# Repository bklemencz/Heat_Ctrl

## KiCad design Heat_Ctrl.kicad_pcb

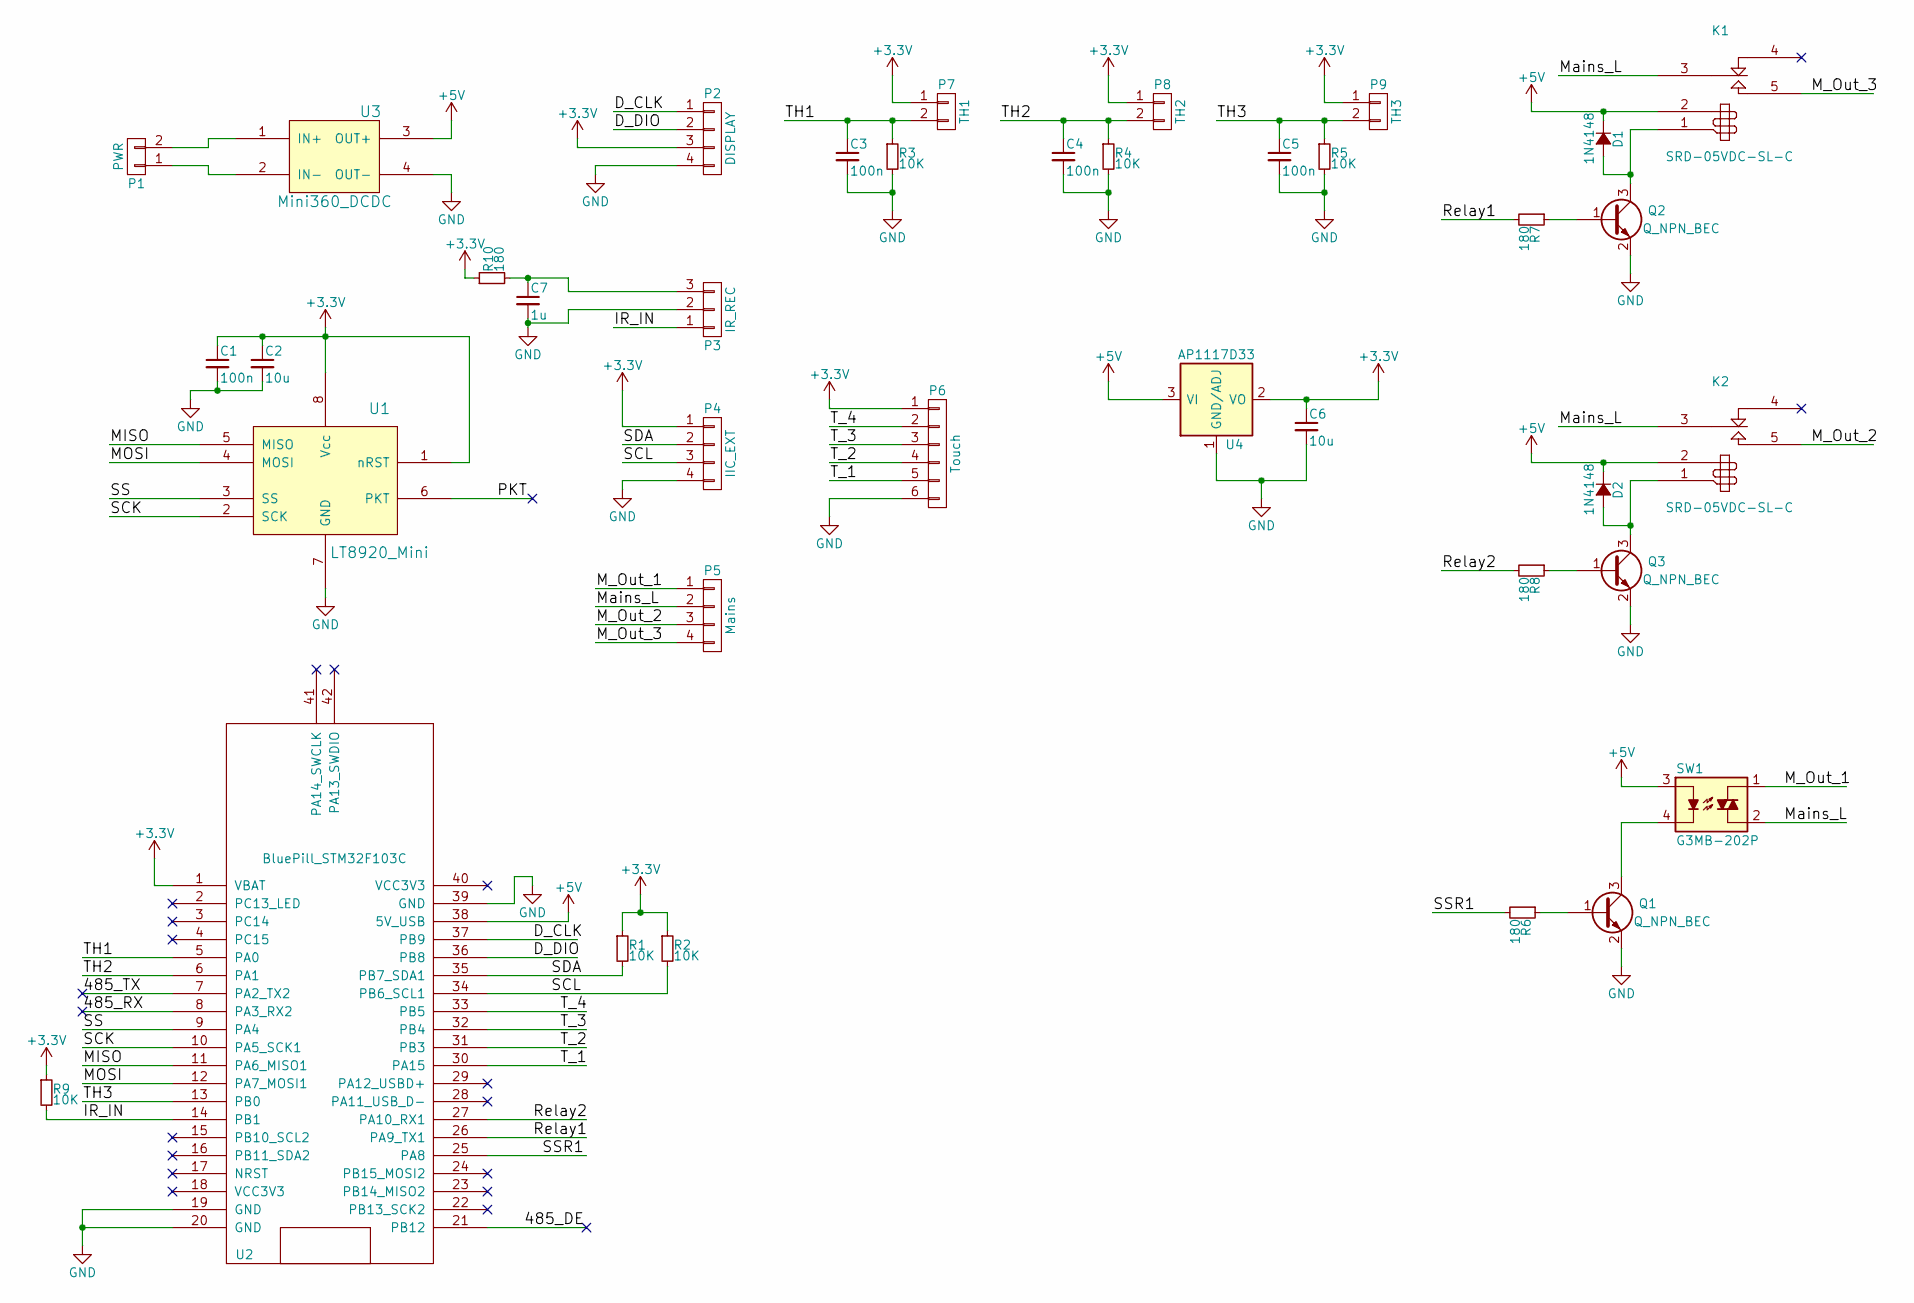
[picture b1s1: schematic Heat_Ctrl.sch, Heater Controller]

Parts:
C1, C3, C4, C5: 100n; C_0805
C2, C6: 10u; C_0805
C7: 1u; C_0805
D1, D2: 1N4148; SOD323
K1, K2: SRD-05VDC-SL-C
P1: PWR; JST_B2B-XH-A
P2: DISPLAY; TM1637_Catalex
P3: IR_REC; 0038_IR_Receiver_SM_Mount
P4: IIC_EXT; JST_B4B-XH-A
P5: Mains; mkds_1,5-4
P6: Touch; JST_B6B-XH-A
P7: TH1; JST_B2B-XH-A
P8: TH2; JST_B2B-XH-A
P9: TH3; JST_B2B-XH-A
Q1, Q2, Q3: Q_NPN_BEC; SOT-23
R1, R2, R3, R4, R5, R9: 10K; R_0805
R6, R7, R8, R10: 180; R_0805
SW1: G3MB-202P
U1: LT8920_Mini; XY-WB_LT8920
U2: BluePill_STM32F103C
U3: Mini360_DCDC
U4: AP1117D33; SOT-223

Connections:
+3V3: C1.1, C2.1, C6.1, P2.3, P4.1, P6.1, P7.1, P8.1, P9.1, R1.1, R2.1, R9.1, R10.1, U1.1 (nRST), U1.8 (Vcc), U2.1 (VBAT), U4.2 (VO)
+5V: D1.1 (K), D2.1 (K), K1.2, K2.2, SW1.3, U2.38 (5V_USB), U3.3 (OUT+), U4.3 (VI)
/485_DE: U2.21 (PB12)
/485_RX: U2.8 (PA3_RX2)
/485_TX: U2.7 (PA2_TX2)
/D_CLK: P2.1, U2.37 (PB9)
/D_DIO: P2.2, U2.36 (PB8)
/IR_IN: P3.1, R9.2, U2.14 (PB1)
/MISO: U1.5 (MISO), U2.11 (PA6_MISO1)
/MOSI: U1.4 (MOSI), U2.12 (PA7_MOSI1)
/M_Out_1: P5.1, SW1.1
/M_Out_2: K2.5, P5.3
/M_Out_3: K1.5, P5.4
/Mains_L: K1.3, K2.3, P5.2, SW1.2
/PKT: U1.6 (PKT)
/Relay1: R7.2, U2.26 (PA9_TX1)
/Relay2: R8.2, U2.27 (PA10_RX1)
/SCK: U1.2 (SCK), U2.10 (PA5_SCK1)
/SCL: P4.3, R2.2, U2.34 (PB6_SCL1)
/SDA: P4.2, R1.2, U2.35 (PB7_SDA1)
/SS: U1.3 (SS), U2.9 (PA4)
/SSR1: R6.2, U2.25 (PA8)
/TH1: C3.1, P7.2, R3.1, U2.5 (PA0)
/TH2: C4.1, P8.2, R4.1, U2.6 (PA1)
/TH3: C5.1, P9.2, R5.1, U2.13 (PB0)
/T_1: P6.5, U2.30 (PA15)
/T_2: P6.4, U2.31 (PB3)
/T_3: P6.3, U2.32 (PB4)
/T_4: P6.2, U2.33 (PB5)
GND: C1.2, C2.2, C3.2, C4.2, C5.2, C6.2, C7.2, P2.4, P3.2, P4.4, P6.6, Q1.2 (E), Q2.2 (E), Q3.2 (E), R3.2, R4.2, R5.2, U1.7 (GND), U2.19 (GND), U2.20 (GND), U2.39 (GND), U3.4 (OUT-), U4.1 (GND/ADJ)
unnamed: C7.1, P3.3, R10.2
unnamed: D1.2 (A), K1.1, Q2.3 (C)
unnamed: D2.2 (A), K2.1, Q3.3 (C)
unnamed: P1.1, U3.2 (IN-)
unnamed: P1.2, U3.1 (IN+)
unnamed: Q1.1 (B), R6.1
unnamed: Q1.3 (C), SW1.4
unnamed: Q2.1 (B), R7.1
unnamed: Q3.1 (B), R8.1

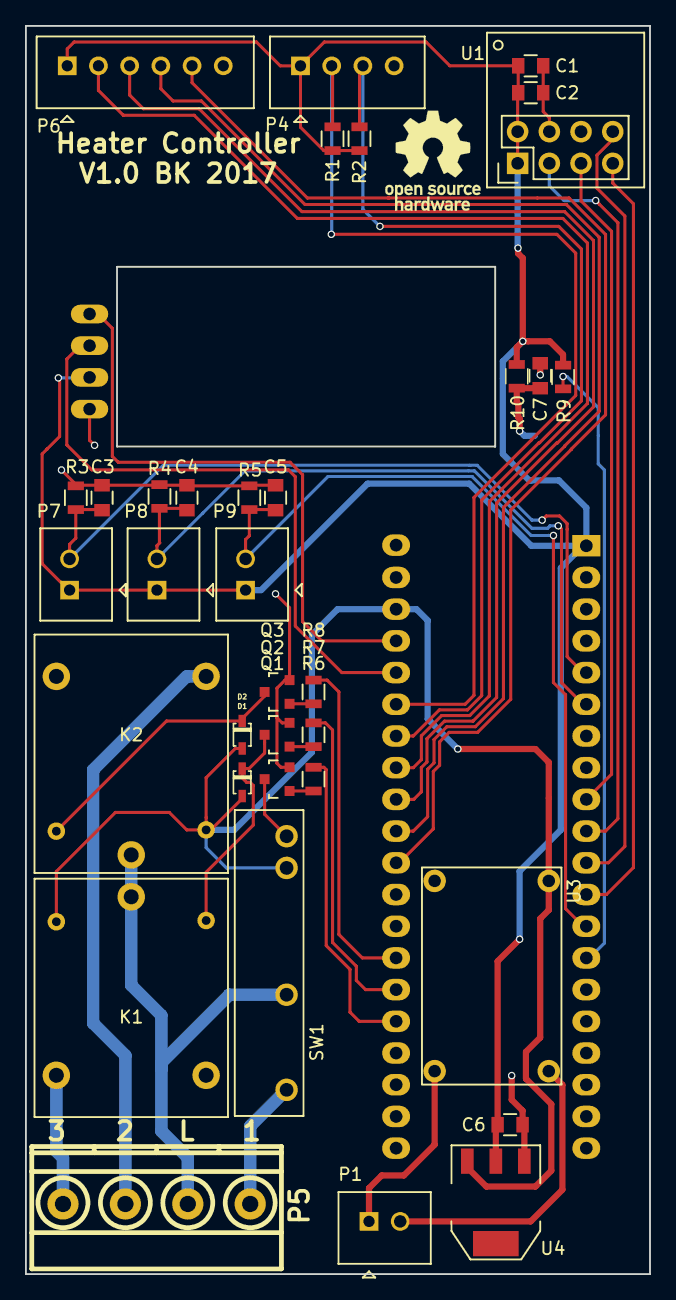
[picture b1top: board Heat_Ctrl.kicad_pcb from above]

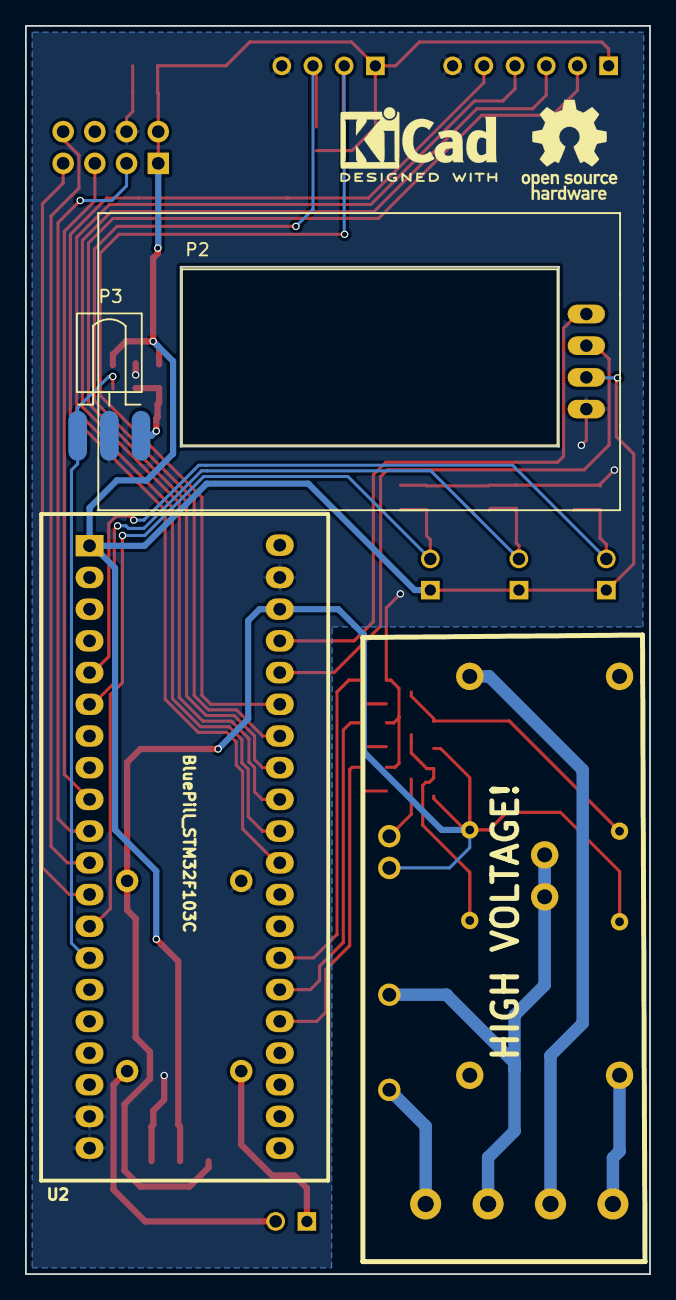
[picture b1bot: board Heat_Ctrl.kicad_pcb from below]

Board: 2 copper layers, 50.0 x 100.0 mm, 38 parts (3 on the bottom side), 35 nets.

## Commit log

2017-11-27 :tada: Added .gitattributes & .gitignore files
2017-11-27 Heater Controller
2017-11-27 Library Update
2017-12-01 IR Receiver Updates
    Add pullup and buffer cap to IR receiver
2017-12-01 IR Update
2017-12-02 Display Change to TH
2017-12-04 PCB Update
